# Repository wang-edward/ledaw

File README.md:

# ledaw

run desktop app
```sh
cargo run
```

build
```sh
cargo build
```

build firmware
```sh
cargo build -p firmware
```

test
```sh
cargo test
```

lint + format
```sh
# rustup component add clippy rustfmt  # if you don't have it
cargo clippy --all-targets --all-features
cargo fmt --check
```

## Firmware

see [`firmware/README.md`](firmware/README.md) for flashing the rp2350.

## pics

## Video demo

## Video demo 2 (art project)

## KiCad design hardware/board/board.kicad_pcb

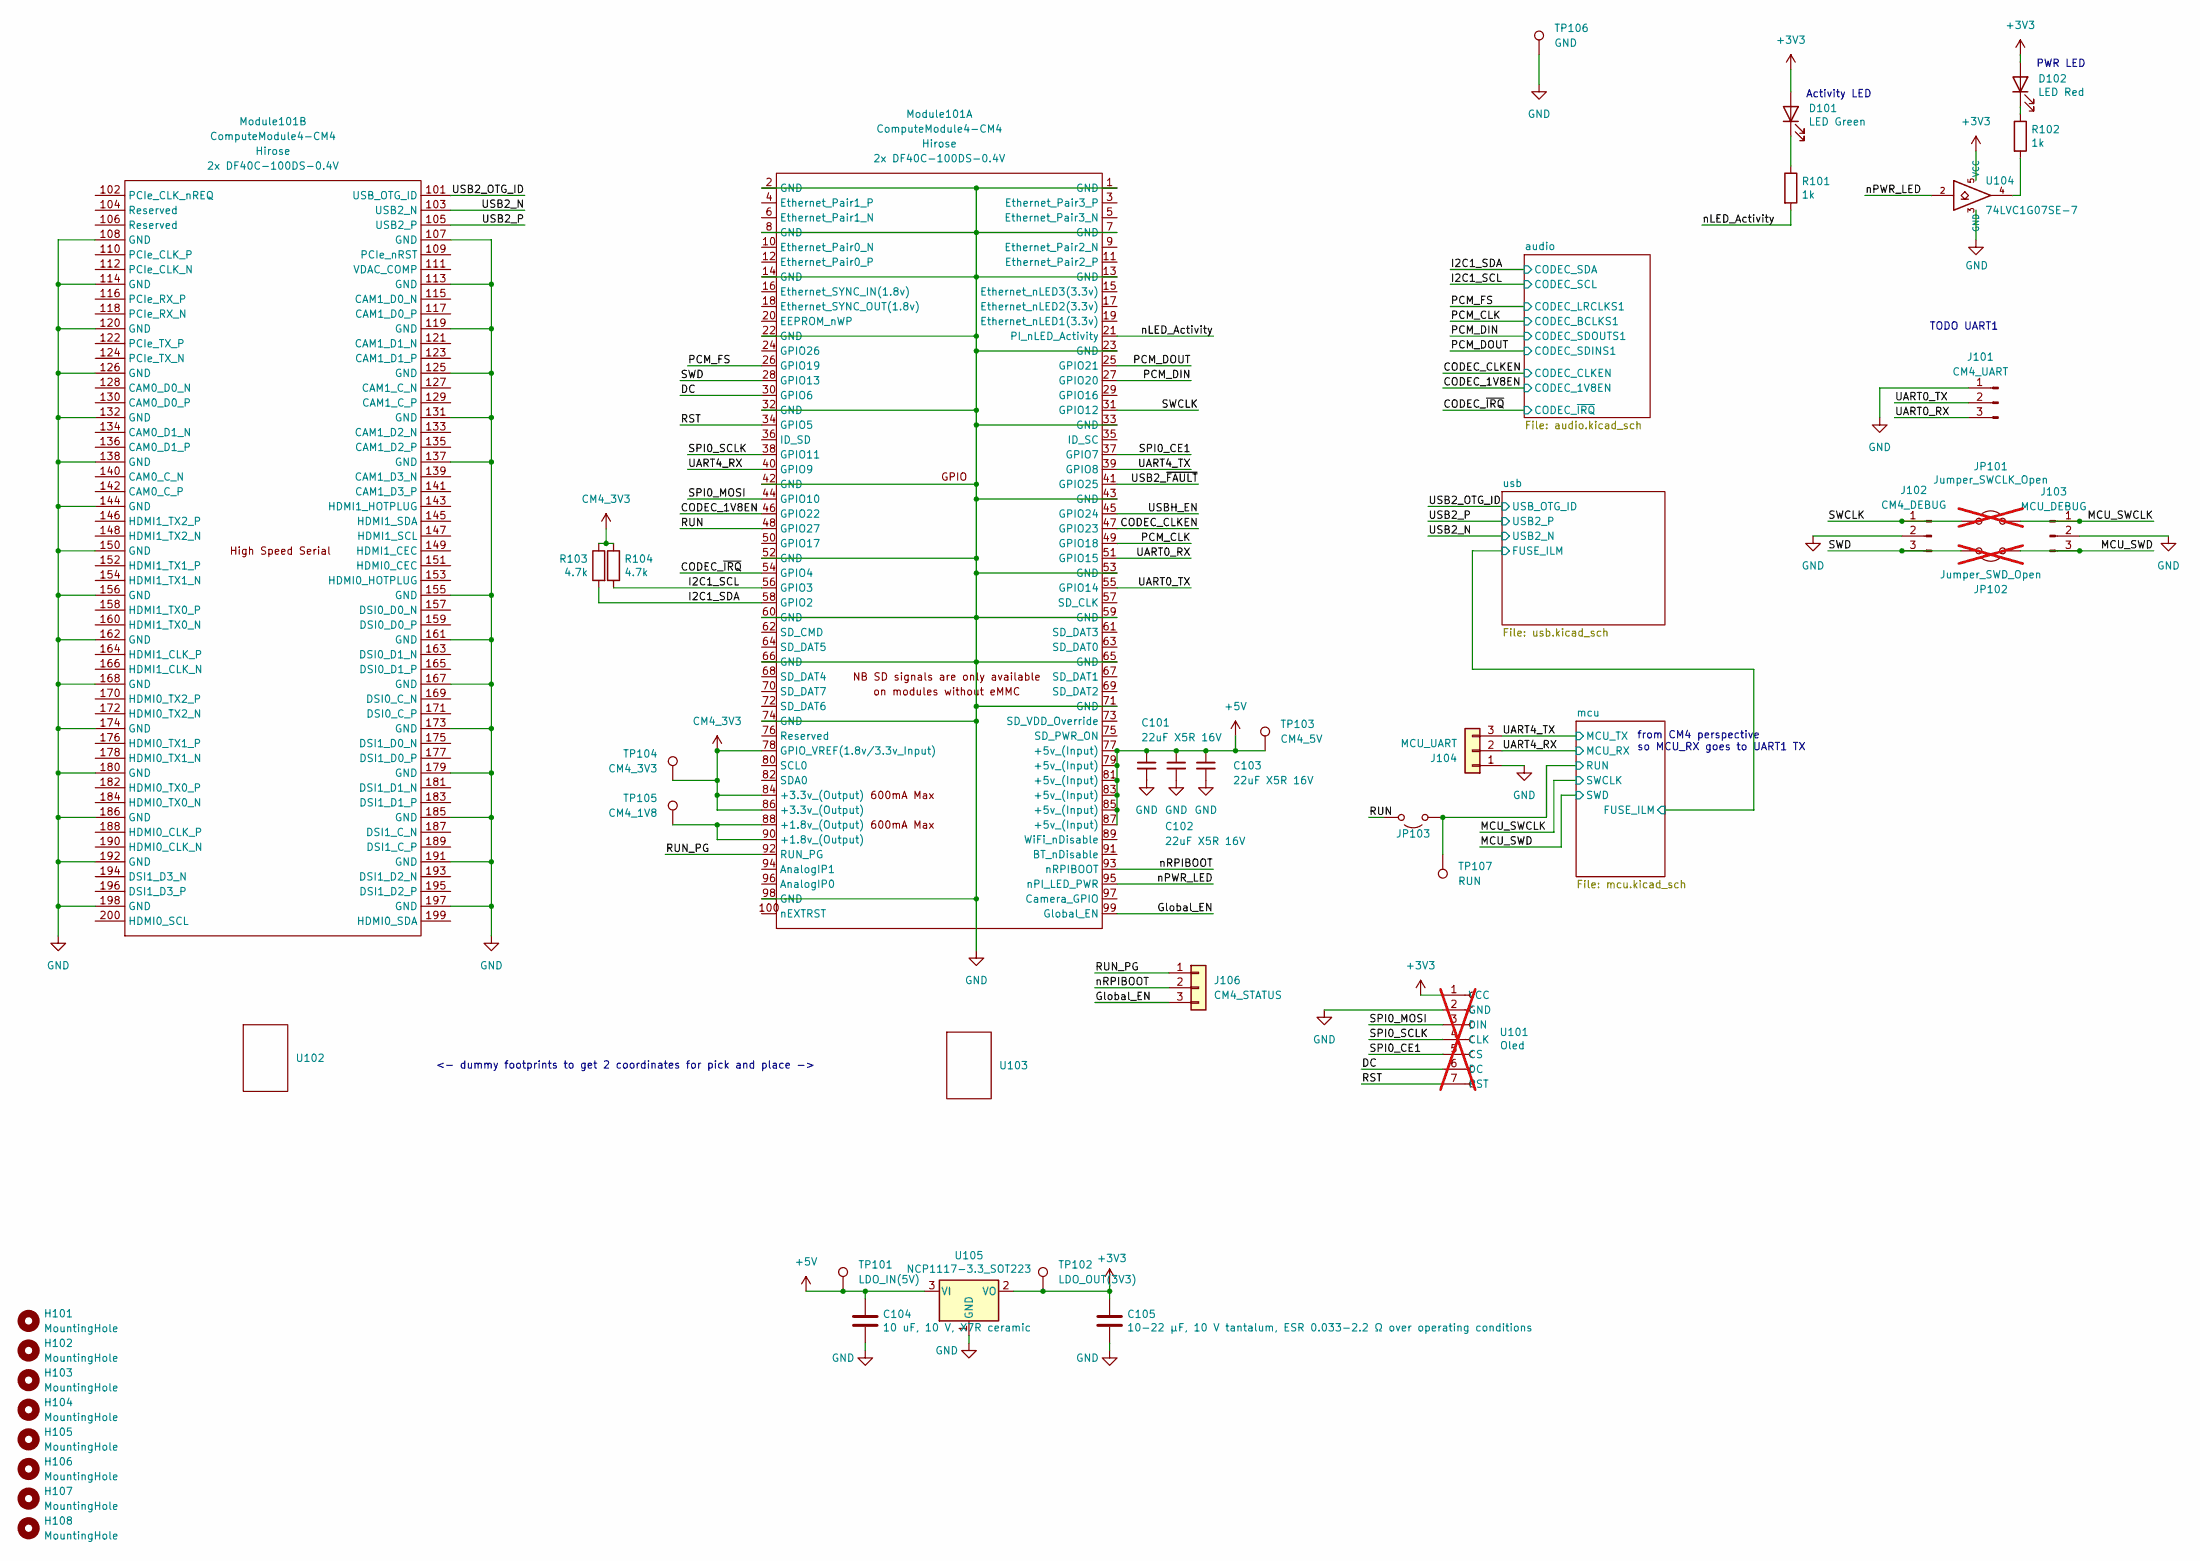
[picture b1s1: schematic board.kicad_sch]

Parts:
C101, C102, C103: 22uF X5R 16V; C_1206_3216Metric; LCSC C90146
C104: 10 uF, 10 V, X7R ceramic; C_0805_2012Metric; MPN TCC0805X7R106K100FT; LCSC C380346
C105: 10-22 µF, 10 V tantalum, ESR 0.033-2.2 Ω over ope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; CP_EIA-3528-21_Kemet-B; LCSC C400102
D101: LED Green; LED_0805_2012Metric; Part Description Green LED, 0805, Vf 2.6-3.1 V at 5 mA; LCSC C2297
D102: LED Red; LED_0805_2012Metric; Part Description Red LED, 0805; LCSC C84256
H101, H102, H103, H104, H105, H106, H107, H108: MountingHole; MountingHole_3.2mm_M3
J101: CM4_UART; named_PinSocket_01x03; LCSC C52016391
J102: CM4_DEBUG; named_PinSocket_01x03; LCSC C52016391
J103: MCU_DEBUG; named_PinSocket_01x03; LCSC C52016391
J104: MCU_UART; named_PinSocket_01x03; MPN HX PH254-01-03-Z-L11.5; LCSC C52016391
J106: CM4_STATUS; named_PinSocket_01x03; MPN HX PH254-01-03-Z-L11.5; LCSC C52016391
JP101: Jumper_SWCLK_Open; SolderJumper-2_P1.3mm_Open_TrianglePad1.0x1.5mm; not fitted
JP102: Jumper_SWD_Open; SolderJumper-2_P1.3mm_Open_TrianglePad1.0x1.5mm; not fitted
JP103: Jumper_SWCLK_Open; SolderJumper-2_P1.3mm_Open_TrianglePad1.0x1.5mm
Module101: ComputeModule4-CM4; Raspberry-Pi-4-Compute-Module
R101, R102: 1k; R_0805_2012Metric; MPN 0805W8F1001T5E; LCSC C17513
R103, R104: 4.7k; R_0805_2012Metric; MPN 0805W8F4701T5E; LCSC C17673
TP101: LDO_IN(5V); named_TestPoint
TP102: LDO_OUT(3V3); named_TestPoint
TP103: CM4_5V; named_TestPoint
TP104: CM4_3V3; named_TestPoint
TP105: CM4_1V8; named_TestPoint
TP106: GND; named_TestPoint
TP107: RUN; named_TestPoint
U101: Oled; waveshare-1.5inch-oled; not fitted
U102, U103: dummy_hirose; LCSC C597931
U104: 74LVC1G07SE-7; SOT-353_SC-70-5; Part Description Buffer, Non-Inverting 1 Element 1 Bit p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; LCSC C67531
U105: NCP1117-3.3_SOT223; SOT-223-3_TabPin2; MPN NCP1117ST33T3G; LCSC C26537

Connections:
+3V3: C105.1, D101.2 (A), D102.2 (A), TP102.1 (1_1), U101.1 (VCC), U104.5 (VCC), U105.2 (VO); also elsewhere on the board
+5V: C101.1, C102.1, C103.1, C104.1, Module101.77 (+5v_(Input)), Module101.79 (+5v_(Input)), Module101.81 (+5v_(Input)), Module101.83 (+5v_(Input)), Module101.85 (+5v_(Input)), Module101.87 (+5v_(Input)), TP101.1 (1_1), TP103.1 (1_1), U105.3 (VI); also elsewhere on the board
/CODEC_1V8EN: Module101.46 (GPIO22); also elsewhere on the board
/CODEC_CLKEN: Module101.47 (GPIO23); also elsewhere on the board
/CODEC_~IRQ: Module101.54 (GPIO4); also elsewhere on the board
/DC: Module101.30 (GPIO6), U101.6 (DC)
/Global_EN: J106.3, Module101.99 (Global_EN)
/I2C1_SCL: Module101.56 (GPIO3), R104.2; also elsewhere on the board
/I2C1_SDA: Module101.58 (GPIO2), R103.2; also elsewhere on the board
/MCU_SWCLK: J103.1, JP101.2 (B); also elsewhere on the board
/MCU_SWD: J103.3, JP102.2 (B); also elsewhere on the board
/PCM_CLK: Module101.49 (GPIO18); also elsewhere on the board
/PCM_DIN: Module101.27 (GPIO20); also elsewhere on the board
/PCM_DOUT: Module101.25 (GPIO21); also elsewhere on the board
/PCM_FS: Module101.26 (GPIO19); also elsewhere on the board
/RST: Module101.34 (GPIO5), U101.7 (RST)
/RUN: JP103.2 (B), Module101.48 (GPIO27)
/RUN_PG: J106.1, Module101.92 (RUN_PG)
/SPI0_CE1: Module101.37 (GPIO7), U101.5 (CS)
/SPI0_MOSI: Module101.44 (GPIO10), U101.3 (DIN)
/SPI0_SCLK: Module101.38 (GPIO11), U101.4 (CLK)
/SWCLK: J102.1, JP101.1 (A), Module101.31 (GPIO12)
/SWD: J102.3, JP102.1 (A), Module101.28 (GPIO13)
/UART0_RX: J101.3, Module101.51 (GPIO15)
/UART0_TX: J101.2, Module101.55 (GPIO14)
/UART4_RX: J104.2, Module101.40 (GPIO9); also elsewhere on the board
/UART4_TX: J104.3, Module101.39 (GPIO8); also elsewhere on the board
/USB2_N: Module101.103 (USB2_N); also elsewhere on the board
/USB2_OTG_ID: Module101.101 (USB_OTG_ID); also elsewhere on the board
/USB2_P: Module101.105 (USB2_P); also elsewhere on the board
/USB2_~FAULT: Module101.41 (GPIO25)
/USBH_EN: Module101.45 (GPIO24)
/mcu/RUN: JP103.1 (A), TP107.1 (1_1); also elsewhere on the board
/nLED_Activity: Module101.21 (PI_nLED_Activity), R101.2
/nPWR_LED: Module101.95 (nPI_LED_PWR), U104.2
/nRPIBOOT: J106.2, Module101.93 (nRPIBOOT)
CM4_3V3: Module101.78 (GPIO_VREF(1.8v/3.3v_Input)), Module101.84 (+3.3v_(Output)), Module101.86 (+3.3v_(Output)), R103.1, R104.1, TP104.1 (1_1)
unnamed: D101.1 (K), R101.1
unnamed: D102.1 (K), R102.1
unnamed: Module101.88 (+1.8v_(Output)), Module101.90 (+1.8v_(Output)), TP105.1 (1_1)
unnamed: R102.2, U104.4

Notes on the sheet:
<- dummy footprints to get 2 coordinates for pick and place ->
TODO UART1
PWR LED
Activity LED
from CM4 perspective so MCU_RX goes to UART1 TX

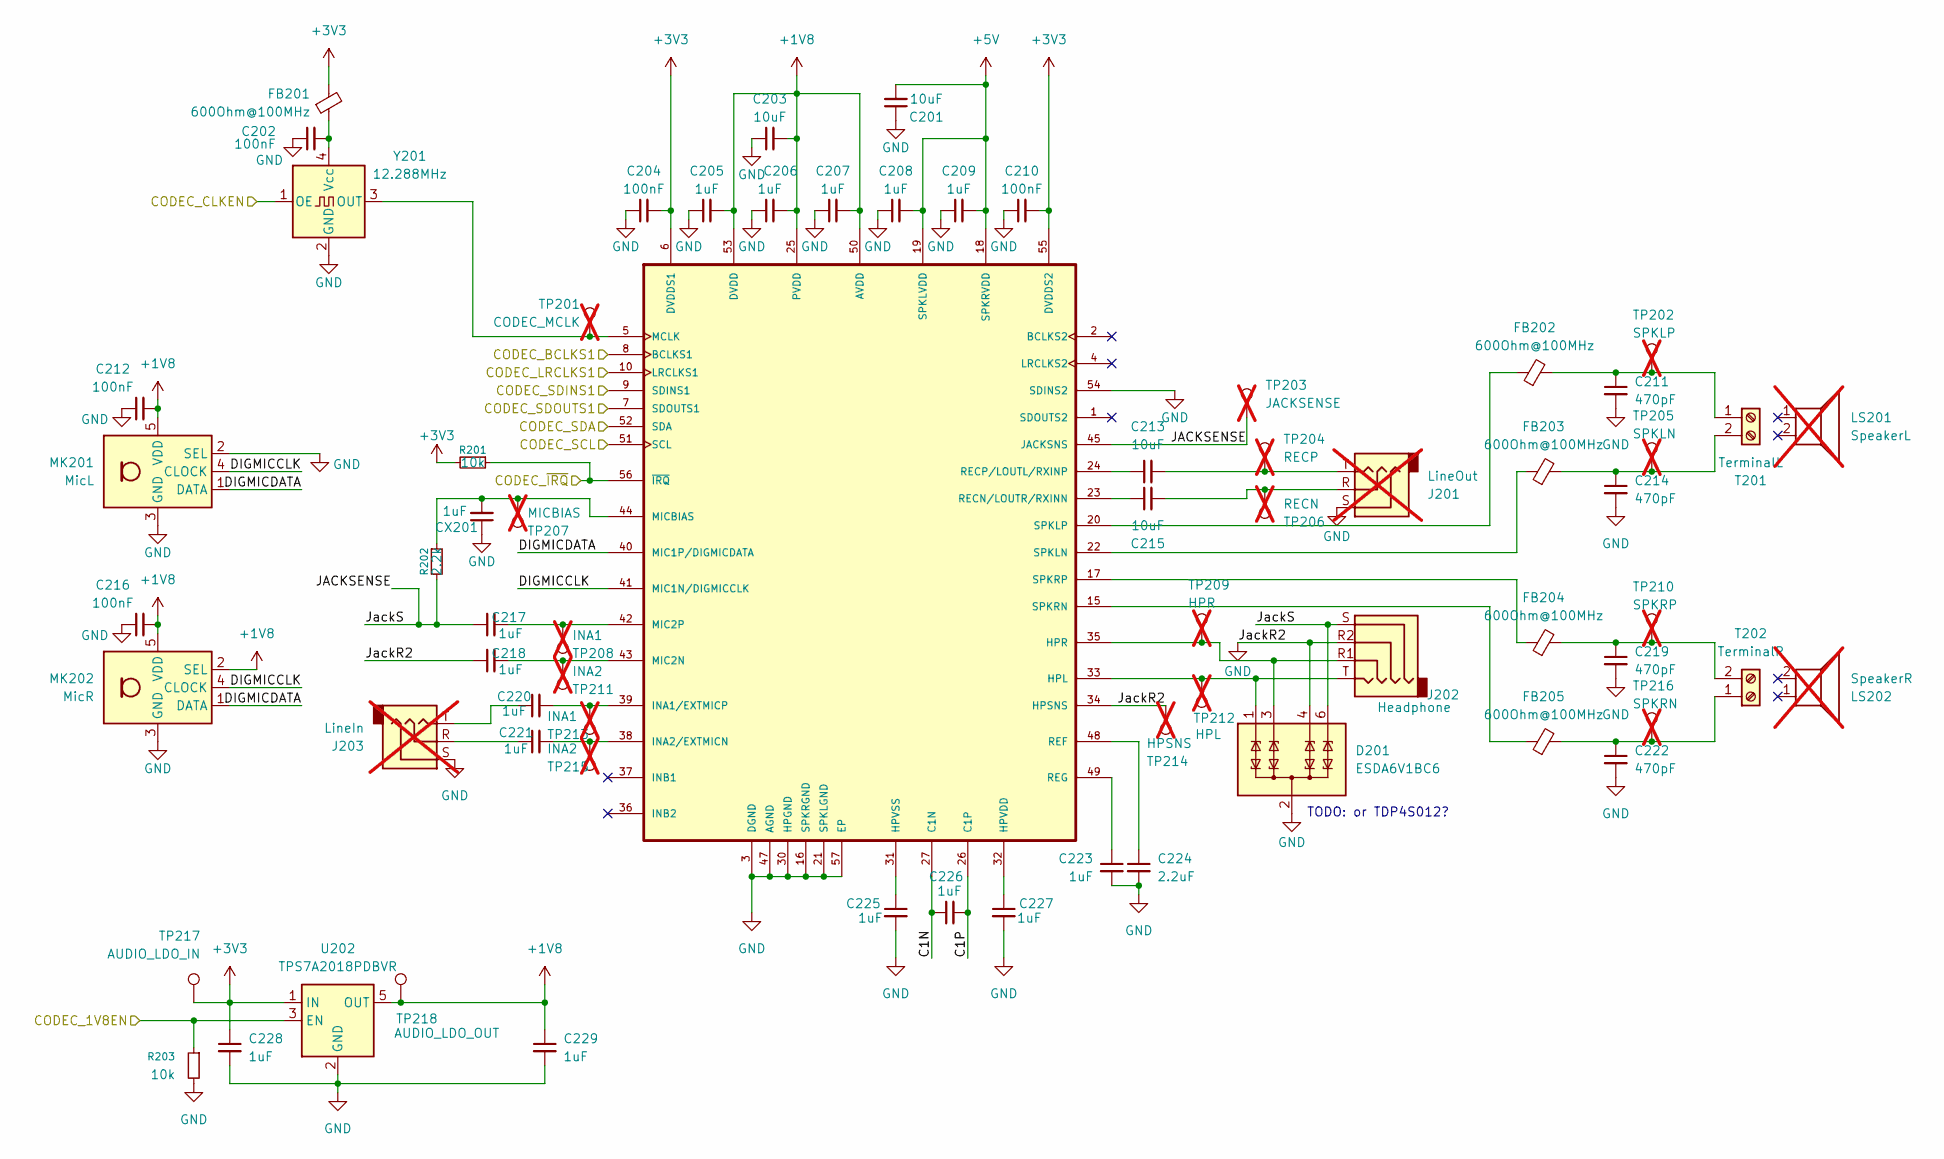
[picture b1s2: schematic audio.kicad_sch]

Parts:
C201, C203, C213, C215: 10uF; C_0805_2012Metric; LCSC C1713
C202, C204, C210, C212, C216: 100nF; C_0805_2012Metric; LCSC C49678
C205, C206, C207, C208, C209, C217, C218, C220, C221, C223, C225, C226, C227, C228, C229: 1uF; C_0805_2012Metric; LCSC C28323
C211, C214, C219, C222: 470pF; C_0805_2012Metric; LCSC C1743
C224: 2.2uF; C_0805_2012Metric; LCSC C377773
CX201: 1uF; C_0805_2012Metric; LCSC C28323
D201: ESDA6V1BC6; SOT-23-6; LCSC C495220
FB201, FB202, FB203, FB204, FB205: 600Ohm@100MHz; L_0805_2012Metric; LCSC C341663
J201: LineOut; Jack_3.5mm_CUI_SJ1-3525N_Horizontal; not fitted
J202: Headphone; CUI_SJ-43514; LCSC C20182909
J203: LineIn; Jack_3.5mm_CUI_SJ1-3525N_Horizontal; not fitted
LS201: SpeakerL; bf-32-s-8ohm; LCSC C474881; not fitted
LS202: SpeakerR; bf-32-s-8ohm; LCSC C474881; not fitted
MK201: MicL; Knowles_LGA-5_3.5x2.65mm; LCSC C2879853
MK202: MicR; Knowles_LGA-5_3.5x2.65mm; LCSC C2879853
R201, R203: 10k; R_0805_2012Metric; LCSC C17414
R202: 2.2k; R_0805_2012Metric; LCSC C17520
T201: TerminalL; TerminalBlock_Phoenix_MKDS-1,5-2-5.08_1x02_P5.08mm_Horizont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; LCSC C5183929
T202: TerminalR; TerminalBlock_Phoenix_MKDS-1,5-2-5.08_1x02_P5.08mm_Horizont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; LCSC C5183929
TP201: CODEC_MCLK; named_TestPoint; not fitted
TP202: SPKLP; named_TestPoint; not fitted
TP203: JACKSENSE; named_TestPoint; not fitted
TP204: RECP; named_TestPoint; not fitted
TP205: SPKLN; named_TestPoint; not fitted
TP206: RECN; named_TestPoint; not fitted
TP207: MICBIAS; named_TestPoint; not fitted
TP208, TP213: INA1; named_TestPoint; not fitted
TP209: HPR; named_TestPoint; not fitted
TP210: SPKRP; named_TestPoint; not fitted
TP211, TP215: INA2; named_TestPoint; not fitted
TP212: HPL; named_TestPoint; not fitted
TP214: HPSNS; named_TestPoint; not fitted
TP216: SPKRN; named_TestPoint; not fitted
TP217: AUDIO_LDO_IN; named_TestPoint
TP218: AUDIO_LDO_OUT; named_TestPoint
U201: MAX98089ETN_T; LCSC C2651816
U202: TPS7A2018PDBVR; SOT-23-5; LCSC C963430
Y201: 12.288MHz; Oscillator_SMD_SeikoEpson_SG210-4Pin_2.5x2.0mm; LCSC C20617595

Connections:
+1V8: C203.2, C205.2, C206.2, C207.2, C212.2, C216.2, C229.1, MK201.5 (VDD), MK202.2 (SEL), MK202.5 (VDD), TP218.1 (1_1), U201.25 (PVDD), U201.50 (AVDD), U201.53 (DVDD), U202.5 (OUT)
+3V3: C204.2, C210.2, C228.1, FB201.2, R201.2, TP217.1 (1_1), U201.6 (DVDDS1), U201.55 (DVDDS2), U202.1 (IN); also elsewhere on the board
+5V: C201.2, C208.2, C209.2, U201.18 (SPKRVDD), U201.19 (SPKLVDD); also elsewhere on the board
/CODEC_1V8EN: R203.1, U202.3 (EN); also elsewhere on the board
/CODEC_CLKEN: Y201.1 (OE); also elsewhere on the board
/CODEC_~IRQ: R201.1, U201.56 (~IRQ); also elsewhere on the board
/I2C1_SCL: U201.51 (SCL); also elsewhere on the board
/I2C1_SDA: U201.52 (SDA); also elsewhere on the board
/PCM_CLK: U201.8 (BCLKS1); also elsewhere on the board
/PCM_DIN: U201.7 (SDOUTS1); also elsewhere on the board
/PCM_DOUT: U201.9 (SDINS1); also elsewhere on the board
/PCM_FS: U201.10 (LRCLKS1); also elsewhere on the board
/audio/C1N: C226.1, U201.27 (C1N)
/audio/C1P: C226.2, U201.26 (C1P)
/audio/DIGMICCLK: MK201.4 (CLOCK), MK202.4 (CLOCK), U201.41 (MIC1N/DIGMICCLK)
/audio/DIGMICDATA: MK201.1 (DATA), MK202.1 (DATA), U201.40 (MIC1P/DIGMICDATA)
unnamed: C213.2, J201.T, TP204.1
unnamed: C215.2, J201.R, TP206.1
unnamed: C220.1, J203.T
unnamed: C221.1, J203.R
unnamed: D201.1 (TVS1), J202.T, TP212.1, U201.33 (HPL)
unnamed: D201.3 (TVS2), J202.R1, TP209.1, U201.35 (HPR)
unnamed: C211.1, FB202.2, T201.1, TP202.1
unnamed: C214.1, FB203.2, T201.2, TP205.1
unnamed: C222.1, FB205.2, T202.1, TP216.1
unnamed: C219.1, FB204.2, T202.2, TP210.1
unnamed: C227.1, U201.32 (HPVDD)
unnamed: C225.1, U201.31 (HPVSS)
unnamed: C220.2, TP213.1, U201.39 (INA1/EXTMICP)
unnamed: C221.2, TP215.1, U201.38 (INA2/EXTMICN)
unnamed: TP201.1 (1_1), U201.5 (MCLK), Y201.3 (OUT)
unnamed: C218.2, TP211.1, U201.43 (MIC2N)
unnamed: C217.2, TP208.1, U201.42 (MIC2P)
unnamed: CX201.2, R202.1, TP207.1 (1_1), U201.44 (MICBIAS)
unnamed: C215.1, U201.23 (RECN/LOUTR/RXINN)
unnamed: C213.1, U201.24 (RECP/LOUTL/RXINP)
unnamed: C224.1, U201.48 (REF)
unnamed: C223.1, U201.49 (REG)
unnamed: FB203.1, U201.22 (SPKLN)
unnamed: FB202.1, U201.20 (SPKLP)
unnamed: FB205.1, U201.15 (SPKRN)
unnamed: FB204.1, U201.17 (SPKRP)
unnamed: C202.2, FB201.1, Y201.4 (Vcc)

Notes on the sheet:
TODO: or TDP4S012?

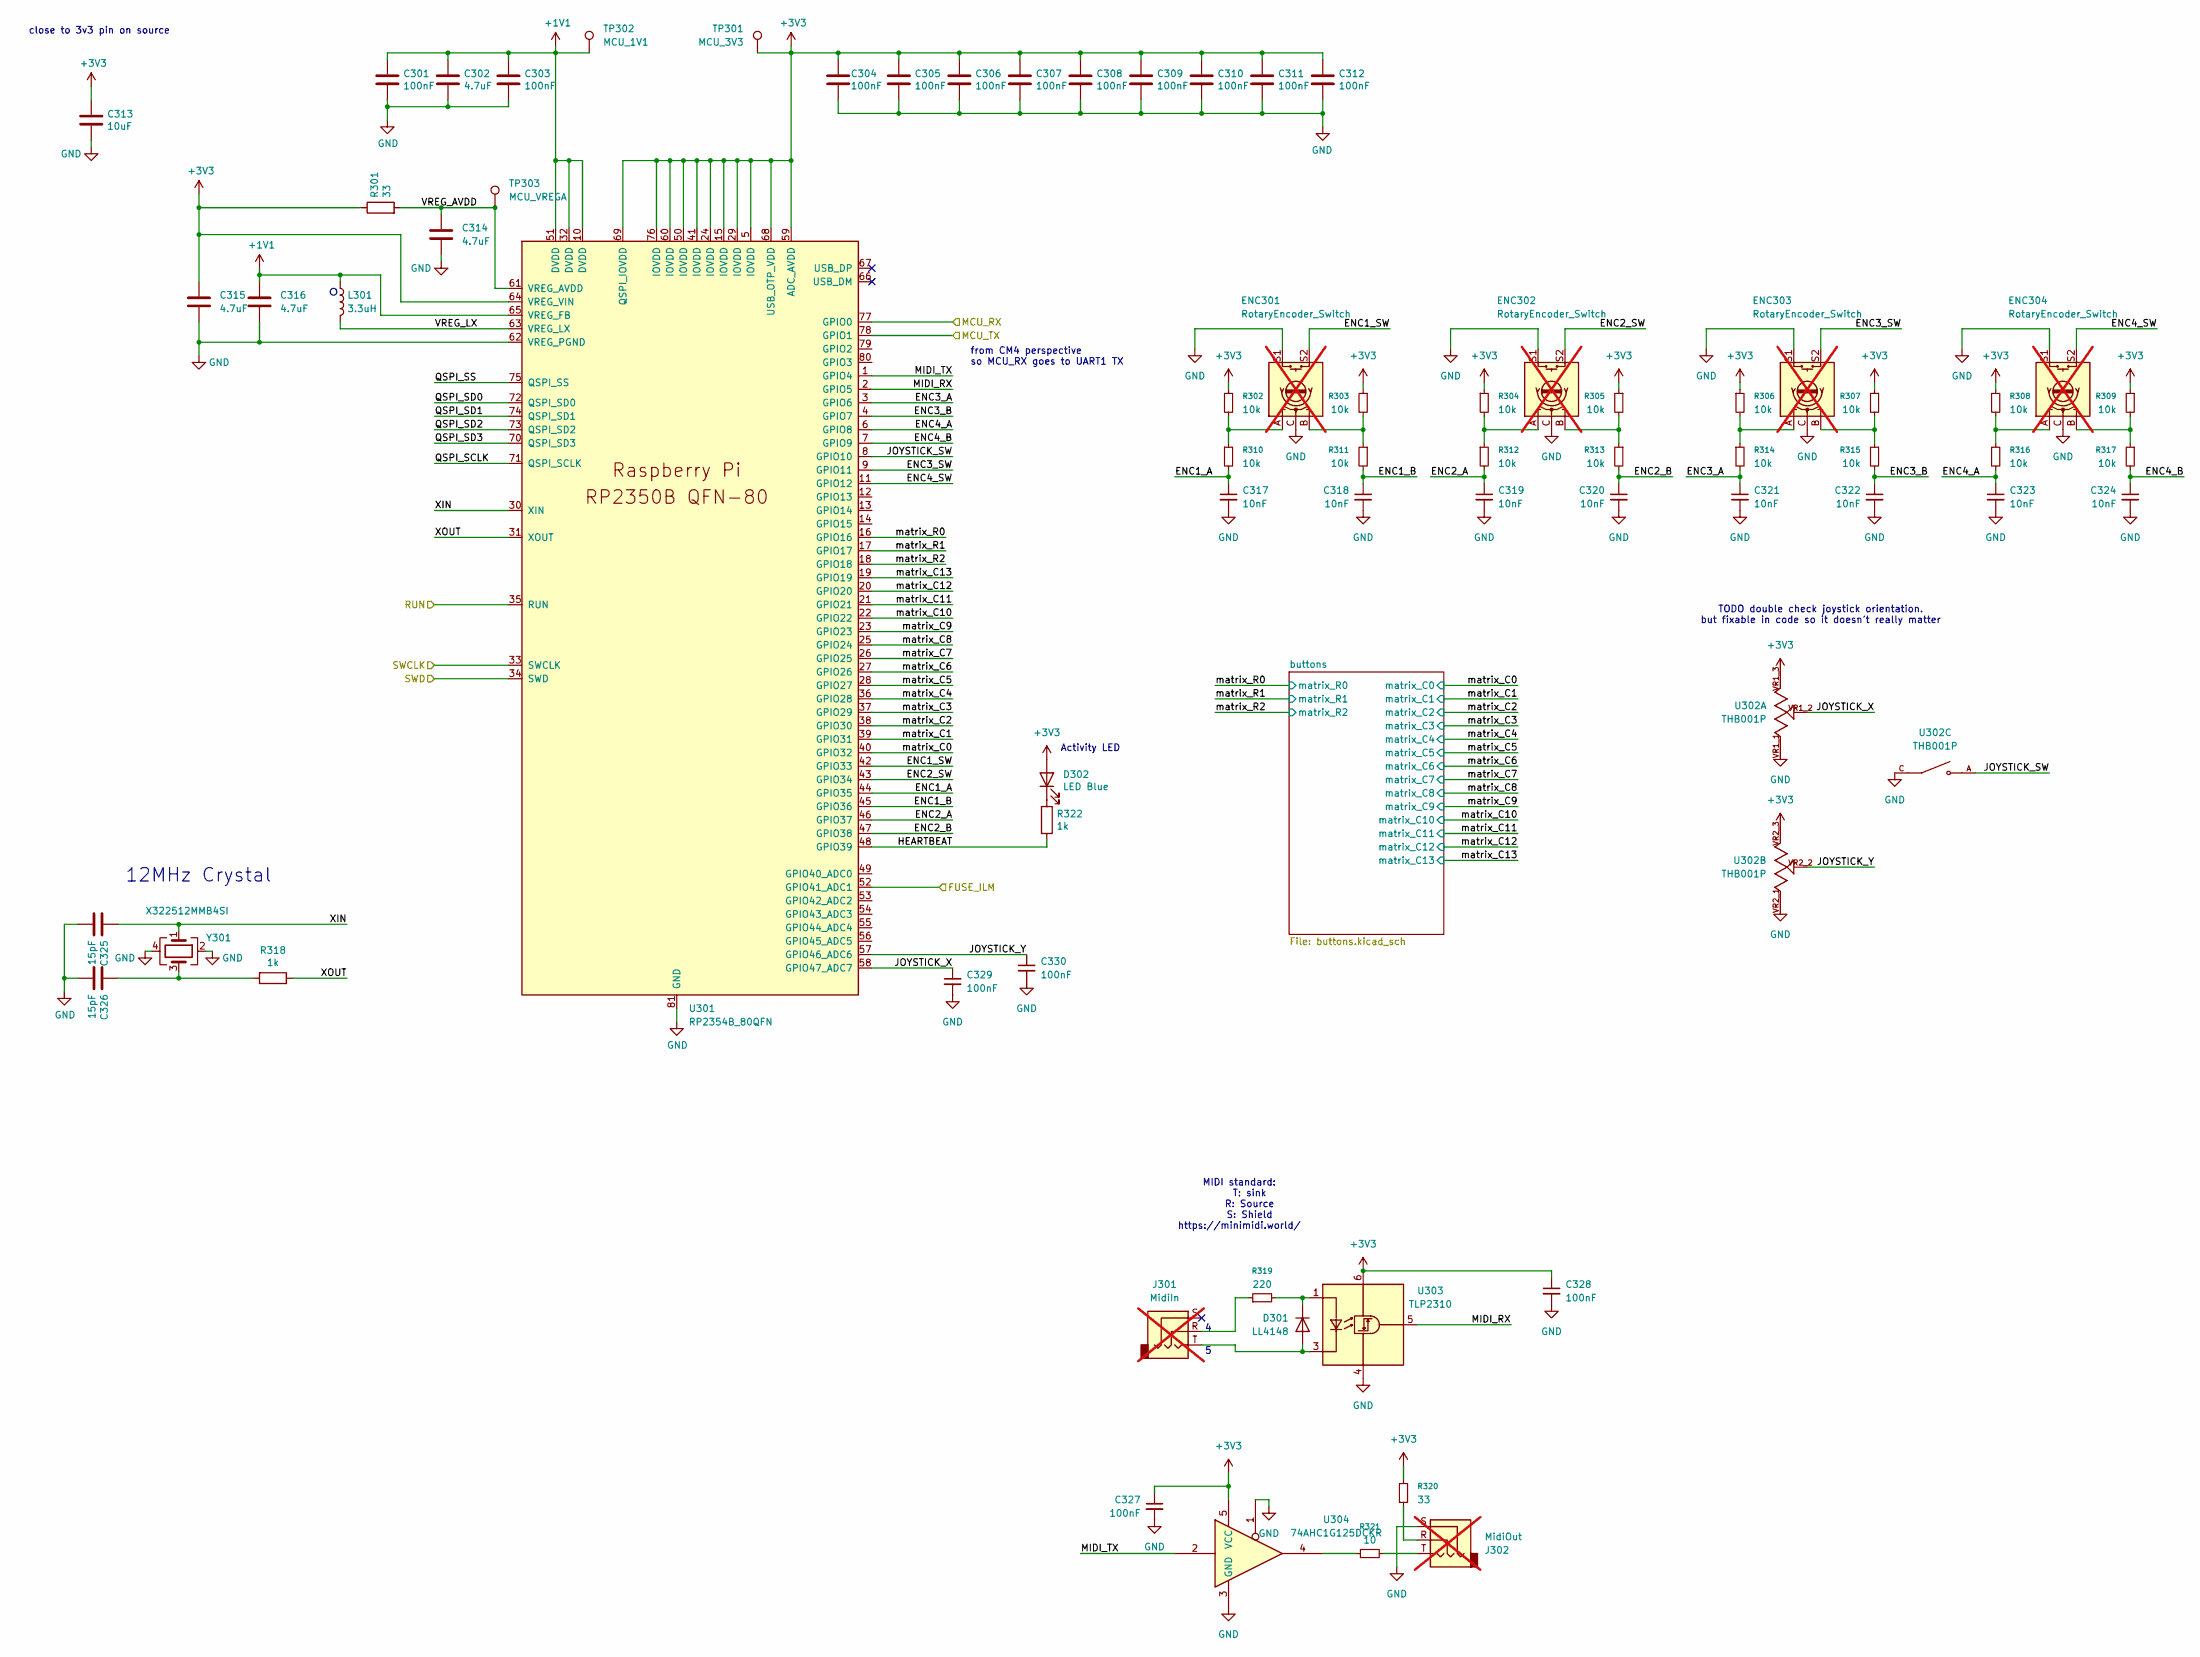
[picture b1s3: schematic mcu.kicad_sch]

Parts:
C301, C303, C304, C305, C306, C307, C308, C309, C310, C311, C312: 100nF; C_0402_1005Metric; LCSC C1525
C302, C314: 4.7uF; C_0402_1005Metric; LCSC C23733
C313: 10uF; C_0805_2012Metric; LCSC C1713
C315, C316: 4.7uF; C_0402_1005Metric_small_pads; LCSC C23733
C317, C318, C319, C320, C321, C322, C323, C324: 10nF; C_0805_2012Metric; LCSC C1710
C325, C326: 15pF; C_0402_1005Metric; LCSC C86285
C327, C328, C329, C330: 100nF; C_0805_2012Metric; LCSC C49678
D301: LL4148; D_MiniMELF; LCSC C78608
D302: LED Blue; LED_0805_2012Metric; Part Description Blue LED, 0805; LCSC C965817
ENC301, ENC302, ENC303, ENC304: RotaryEncoder_Switch; XDCR_PEC11R-4015F-S0024; not fitted
J301: MidiIn; Jack_3.5mm_CUI_SJ1-3525N_Horizontal; not fitted
J302: MidiOut; Jack_3.5mm_CUI_SJ1-3525N_Horizontal; not fitted
L301: 3.3uH; L_pol_2016; LCSC C42411119
R301: 33; R_0402_1005Metric; MPN RC0402FR-0733RL; LCSC C138002
R302, R303, R304, R305, R306, R307, R308, R309, R310, R311, R312, R313, R314, R315, R316, R317: 10k; R_0805_2012Metric; LCSC C17414
R318: 1k; R_0402_1005Metric; MPN RC0402FR-071KL; LCSC C106235
R319: 220; R_0805_2012Metric; LCSC C17557
R320: 33; R_0805_2012Metric; LCSC C17634
R321: 10; R_0805_2012Metric; LCSC C17415
R322: 1k; R_0603_1608Metric_Pad0.98x0.95mm_HandSolder; MPN RC0603FR-071KL; LCSC C22548
TP301: MCU_3V3; named_TestPoint
TP302: MCU_1V1; named_TestPoint
TP303: MCU_VREGA; named_TestPoint
U301: RP2354B_80QFN; RP2350-QFN-80-1EP_10x10_P0.4mm_EP3.4x3.4mm_ThermalVias; LCSC C39843328
U302: THB001P; PARTREV 27 Jan 22; LCSC C2685355
U303: TLP2310; SO-5-6_4.55x3.7mm_P1.27mm; LCSC C7473281
U304: 74AHC1G125DCKR; SOT-353_SC-70-5; LCSC C151890
Y301: X322512MMB4SI; Crystal_SMD_3225-4Pin_3.2x2.5mm; LCSC C50430

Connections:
+1V1: C301.1, C302.1, C303.1, C316.1, L301.1, TP302.1 (1_1), U301.10 (DVDD), U301.32 (DVDD), U301.51 (DVDD), U301.65 (VREG_FB)
+3V3: C304.1, C305.1, C306.1, C307.1, C308.1, C309.1, C310.1, C311.1, C312.1, C313.1, C315.1, C327.1, C328.1, D302.2 (A), R301.1, R302.1, R303.1, R304.1, R305.1, R306.1, R307.1, R308.1, R309.1, R320.2, TP301.1 (1_1), U301.5 (IOVDD), U301.15 (IOVDD), U301.24 (IOVDD), U301.29 (IOVDD), U301.41 (IOVDD), U301.50 (IOVDD), U301.59 (ADC_AVDD), U301.60 (IOVDD), U301.64 (VREG_VIN), U301.68 (USB_OTP_VDD), U301.69 (QSPI_IOVDD), U301.76 (IOVDD), U302.VR1_3, U302.VR2_3, U303.6 (VDD), U304.5 (VCC); also elsewhere on the board
/MCU_SWCLK: U301.33 (SWCLK); also elsewhere on the board
/MCU_SWD: U301.34 (SWD); also elsewhere on the board
/UART4_RX: U301.77 (GPIO0); also elsewhere on the board
/UART4_TX: U301.78 (GPIO1); also elsewhere on the board
/mcu/ENC1_A: C317.1, R310.2, U301.44 (GPIO35)
/mcu/ENC1_B: C318.1, R311.2, U301.45 (GPIO36)
/mcu/ENC1_SW: ENC301.S2, U301.42 (GPIO33)
/mcu/ENC2_A: C319.1, R312.2, U301.46 (GPIO37)
/mcu/ENC2_B: C320.1, R313.2, U301.47 (GPIO38)
/mcu/ENC2_SW: ENC302.S2, U301.43 (GPIO34)
/mcu/ENC3_A: C321.1, R314.2, U301.3 (GPIO6)
/mcu/ENC3_B: C322.1, R315.2, U301.4 (GPIO7)
/mcu/ENC3_SW: ENC303.S2, U301.9 (GPIO11)
/mcu/ENC4_A: C323.1, R316.2, U301.6 (GPIO8)
/mcu/ENC4_B: C324.1, R317.2, U301.7 (GPIO9)
/mcu/ENC4_SW: ENC304.S2, U301.11 (GPIO12)
/mcu/FUSE_ILM: U301.52 (GPIO41_ADC1); also elsewhere on the board
/mcu/HEARTBEAT: R322.2, U301.48 (GPIO39)
/mcu/JOYSTICK_SW: U301.8 (GPIO10), U302.A, U302.B
/mcu/JOYSTICK_X: C329.1, U301.58 (GPIO47_ADC7), U302.VR1_2
/mcu/JOYSTICK_Y: C330.1, U301.57 (GPIO46_ADC6), U302.VR2_2
/mcu/MIDI_RX: U301.2 (GPIO5), U303.5 (VO)
/mcu/MIDI_TX: U301.1 (GPIO4), U304.2
/mcu/QSPI_SCLK: U301.71 (QSPI_SCLK)
/mcu/QSPI_SD0: U301.72 (QSPI_SD0)
/mcu/QSPI_SD1: U301.74 (QSPI_SD1)
/mcu/QSPI_SD2: U301.73 (QSPI_SD2)
/mcu/QSPI_SD3: U301.70 (QSPI_SD3)
/mcu/QSPI_SS: U301.75 (QSPI_SS)
/mcu/RUN: U301.35 (RUN); also elsewhere on the board
/mcu/VREG_AVDD: C314.1, R301.2, TP303.1 (1_1), U301.61 (VREG_AVDD)
/mcu/VREG_LX: L301.2, U301.63 (VREG_LX)
/mcu/XIN: C325.1, U301.30 (XIN), Y301.1
/mcu/XOUT: R318.1, U301.31 (XOUT)
/mcu/matrix_C0: U301.40 (GPIO32); also elsewhere on the board
/mcu/matrix_C1: U301.39 (GPIO31); also elsewhere on the board
/mcu/matrix_C2: U301.38 (GPIO30); also elsewhere on the board
/mcu/matrix_C3: U301.37 (GPIO29); also elsewhere on the board
/mcu/matrix_C4: U301.36 (GPIO28); also elsewhere on the board
/mcu/matrix_C5: U301.28 (GPIO27); also elsewhere on the board
/mcu/matrix_C6: U301.27 (GPIO26); also elsewhere on the board
/mcu/matrix_C7: U301.26 (GPIO25); also elsewhere on the board
/mcu/matrix_C8: U301.25 (GPIO24); also elsewhere on the board
/mcu/matrix_C9: U301.23 (GPIO23); also elsewhere on the board
/mcu/matrix_C10: U301.22 (GPIO22); also elsewhere on the board
/mcu/matrix_C11: U301.21 (GPIO21); also elsewhere on the board
/mcu/matrix_C12: U301.20 (GPIO20); also elsewhere on the board
/mcu/matrix_C13: U301.19 (GPIO19); also elsewhere on the board
/mcu/matrix_R0: U301.16 (GPIO16); also elsewhere on the board
/mcu/matrix_R1: U301.17 (GPIO17); also elsewhere on the board
/mcu/matrix_R2: U301.18 (GPIO18); also elsewhere on the board
unnamed: C326.1, R318.2, Y301.3
unnamed: D301.2 (A), J301.T, U303.3 (K)
unnamed: D301.1 (K), R319.2, U303.1 (A)
unnamed: D302.1 (K), R322.1
unnamed: ENC301.A, R302.2, R310.1
unnamed: ENC301.B, R303.2, R311.1
unnamed: ENC302.A, R304.2, R312.1
unnamed: ENC302.B, R305.2, R313.1
unnamed: ENC303.A, R306.2, R314.1
unnamed: ENC303.B, R307.2, R315.1
unnamed: ENC304.A, R308.2, R316.1
unnamed: ENC304.B, R309.2, R317.1
unnamed: J301.R, R319.1
unnamed: J302.R, R320.1
unnamed: J302.T, R321.2
unnamed: R321.1, U304.4

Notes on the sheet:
TODO double check joystick orientation. but fixable in code so it doesn't really matter
MIDI standard: T: sink R: Source S: Shield https://minimidi.world/
12MHz Crystal
close to 3v3 pin on source
Activity LED
from CM4 perspective so MCU_RX goes to UART1 TX

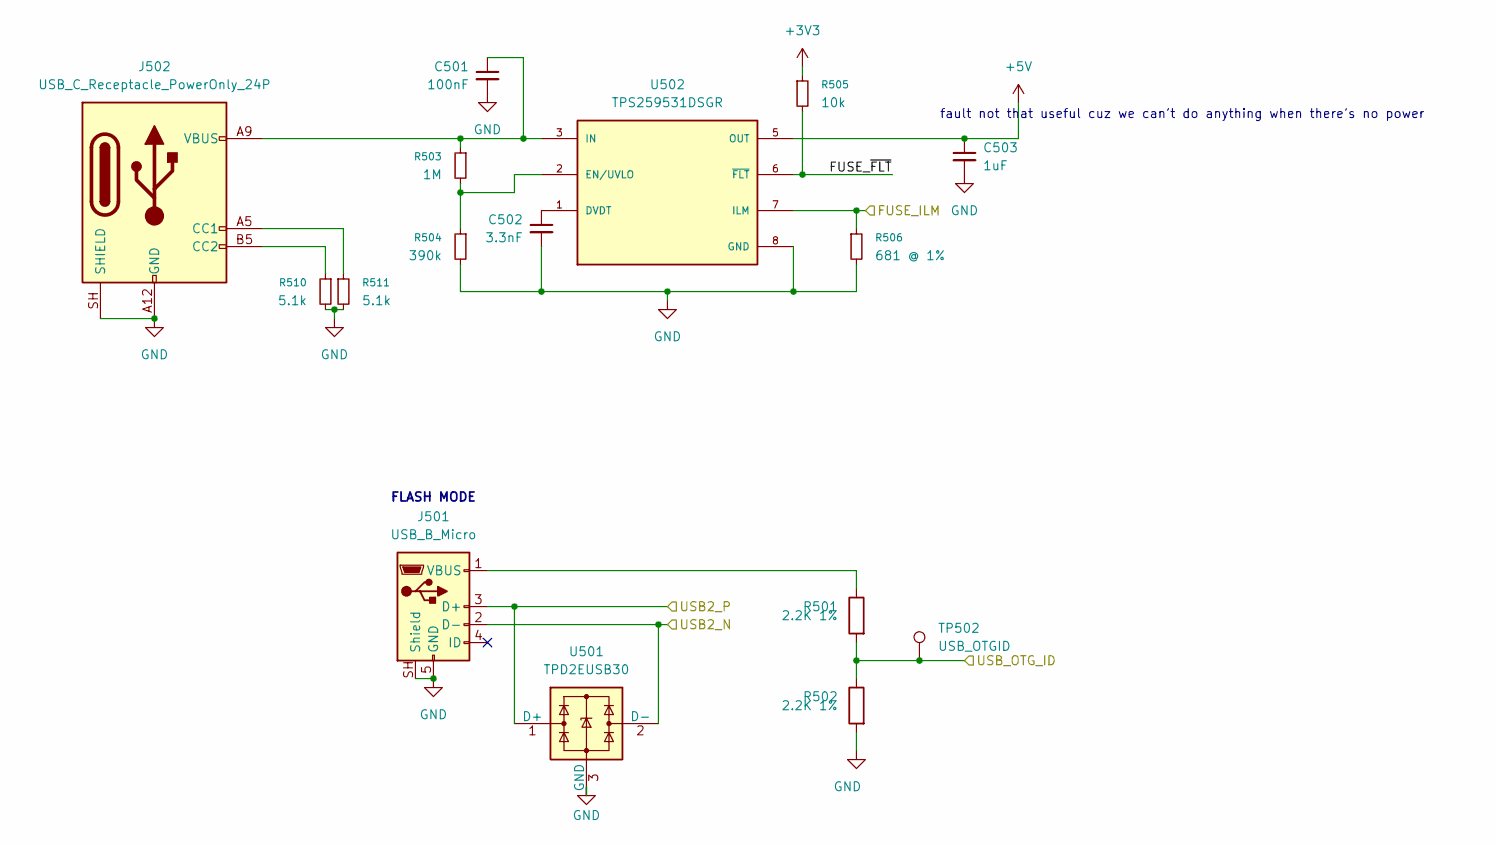
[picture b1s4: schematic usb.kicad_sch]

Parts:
C501: 100nF; C_0805_2012Metric; LCSC C49678
C502: 3.3nF; C_0805_2012Metric; LCSC C1738
C503: 1uF; C_0805_2012Metric; MPN TCC0805X7R105K500DT; LCSC C376926
J501: USB_B_Micro; USB_Micro-B_Molex_47346-0001; LCSC C132560
J502: USB_C_Receptacle_PowerOnly_24P; USB_C_Receptacle_HRO_TYPE-C-31-M-12; LCSC C165948
R501, R502: 2.2K 1%; R_0805_2012Metric; MPN 0805W8F2201T5E; LCSC C17520
R503: 1M; R_0805_2012Metric; MPN 0805W8F1004T5E; LCSC C17514
R504: 390k; R_0805_2012Metric; LCSC C17656
R505: 10k; R_0805_2012Metric; LCSC C17414
R506: 681 @ 1%; R_0805_2012Metric; LCSC C17800
R510, R511: 5.1k; R_0805_2012Metric; LCSC C26023
TP502: USB_OTGID; named_TestPoint
U501: TPD2EUSB30; Texas_DRT-3; MPN TPD2EUSB30DRTR; LCSC C97502
U502: TPS259531DSGR; SON50P200X200X80-9N; PARTREV C; LCSC C2155674

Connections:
+3V3: R505.1; also elsewhere on the board
+5V: C503.1, U502.5 (OUT); also elsewhere on the board
/USB2_N: J501.2 (D-), U501.2 (D-); also elsewhere on the board
/USB2_OTG_ID: R501.2, R502.1, TP502.1 (1_1); also elsewhere on the board
/USB2_P: J501.3 (D+), U501.1 (D+); also elsewhere on the board
/mcu/FUSE_ILM: R506.1, U502.7 (ILM); also elsewhere on the board
/usb/FUSE_~FLT: R505.2, U502.6 (~FLT)
unnamed: C501.1, J502.A4 (VBUS), J502.A9 (VBUS), J502.B4 (VBUS), J502.B9 (VBUS), R503.1, U502.3 (IN), U502.4 (IN)
unnamed: J501.1 (VBUS), R501.1
unnamed: J502.A5 (CC1), R511.1
unnamed: J502.B5 (CC2), R510.1
unnamed: C502.1, U502.1 (DVDT)
unnamed: R503.2, R504.1, U502.2 (EN/UVLO)

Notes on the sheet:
FLASH MODE
fault not that useful cuz we can't do anything when there's no power
